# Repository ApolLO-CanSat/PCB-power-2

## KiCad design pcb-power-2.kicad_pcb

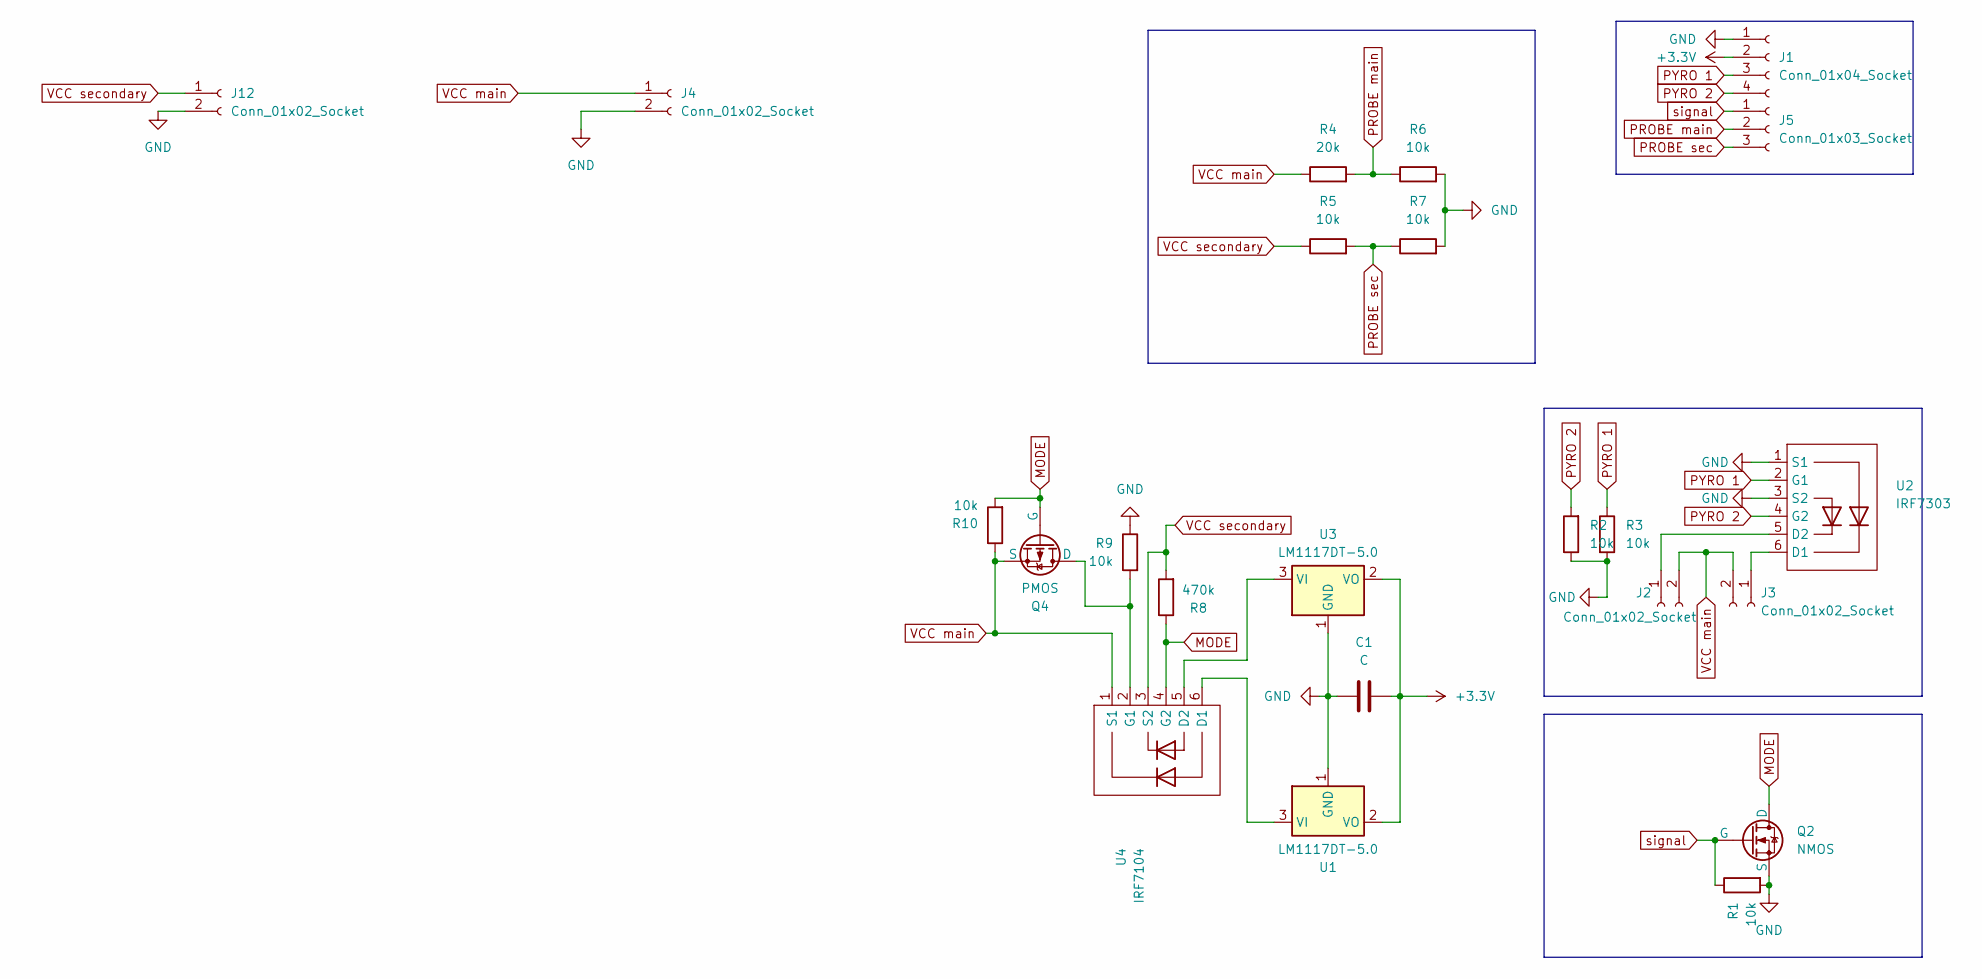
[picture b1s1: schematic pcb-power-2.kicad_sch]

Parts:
C1: C; CP_Radial_D5.0mm_P2.00mm
J1: Conn_01x04_Socket; JST_PH_B4B-PH-K_1x04_P2.00mm_Vertical
J2, J3: Conn_01x02_Socket; TerminalBlock_bornier-2_P5.08mm
J4: Conn_01x02_Socket; JST_PH_B2B-PH-K_1x02_P2.00mm_Vertical
J5: Conn_01x03_Socket; JST_PH_B3B-PH-K_1x03_P2.00mm_Vertical
J12: Conn_01x02_Socket; PinSocket_1x02_P2.54mm_Vertical
Q2: NMOS; SOT-23
Q4: PMOS; TO-252-2
R1, R2, R3, R5, R6, R7, R9, R10: 10k; R_Axial_DIN0207_L6.3mm_D2.5mm_P10.16mm_Horizontal
R4: 20k; R_Axial_DIN0207_L6.3mm_D2.5mm_P10.16mm_Horizontal
R8: 470k; R_Axial_DIN0207_L6.3mm_D2.5mm_P10.16mm_Horizontal
U1, U3: LM1117DT-5.0; TO-252-2
U2: IRF7303
U4: IRF7104

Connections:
+3.3V: C1.2, J1.2, U1.2 (VO), U3.2 (VO)
GND: C1.1, J1.1, J4.2, J12.2, Q2.3 (S), R1.2, R2.1, R3.2, R6.2, R7.2, R9.1, U1.1 (GND), U2.1 (S1), U2.3 (S2), U3.1 (GND)
MODE: Q2.1 (D), Q4.2 (G), R8.1, R10.2, U4.4 (G2)
unnamed: J2.1, U2.5 (D2)
unnamed: J3.1, U2.6 (D1)
unnamed: Q4.1 (D), R9.2, U4.2 (G1)
unnamed: U1.3 (VI), U4.6 (D1)
unnamed: U3.3 (VI), U4.5 (D2)
PROBE main: J5.2, R4.2, R6.1
PROBE sec: J5.3, R5.2, R7.1
PYRO 1: J1.3, R3.1, U2.2 (G1)
PYRO 2: J1.4, R2.2, U2.4 (G2)
VCC main: J2.2, J3.2, J4.1, Q4.3 (S), R4.1, R10.1, U4.1 (S1)
VCC secondary: J12.1, R5.1, R8.2, U4.3 (S2)
signal: J5.1, Q2.2 (G), R1.1

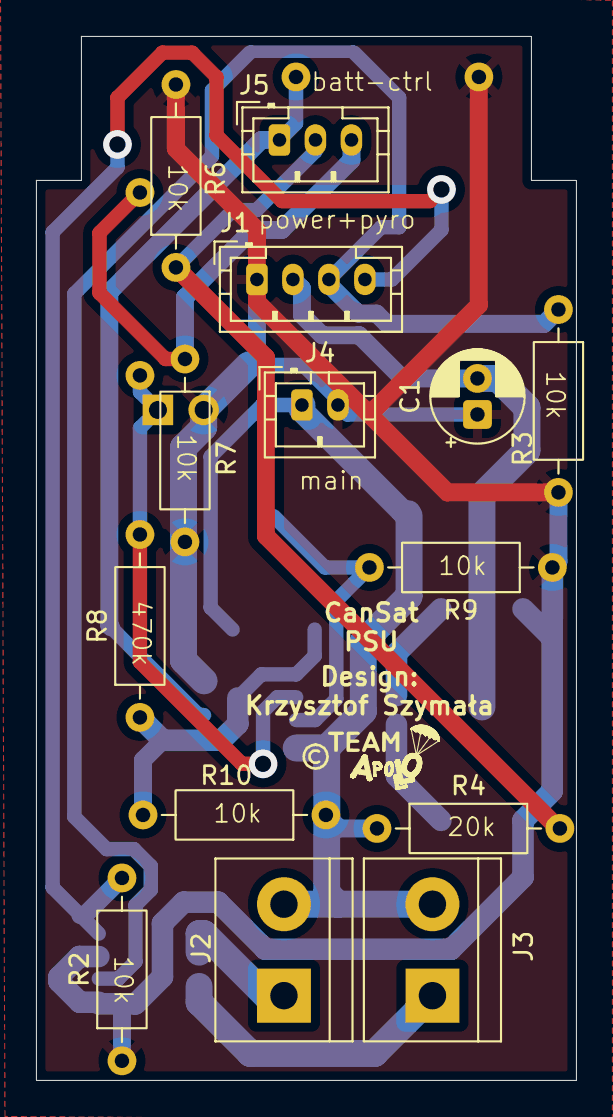
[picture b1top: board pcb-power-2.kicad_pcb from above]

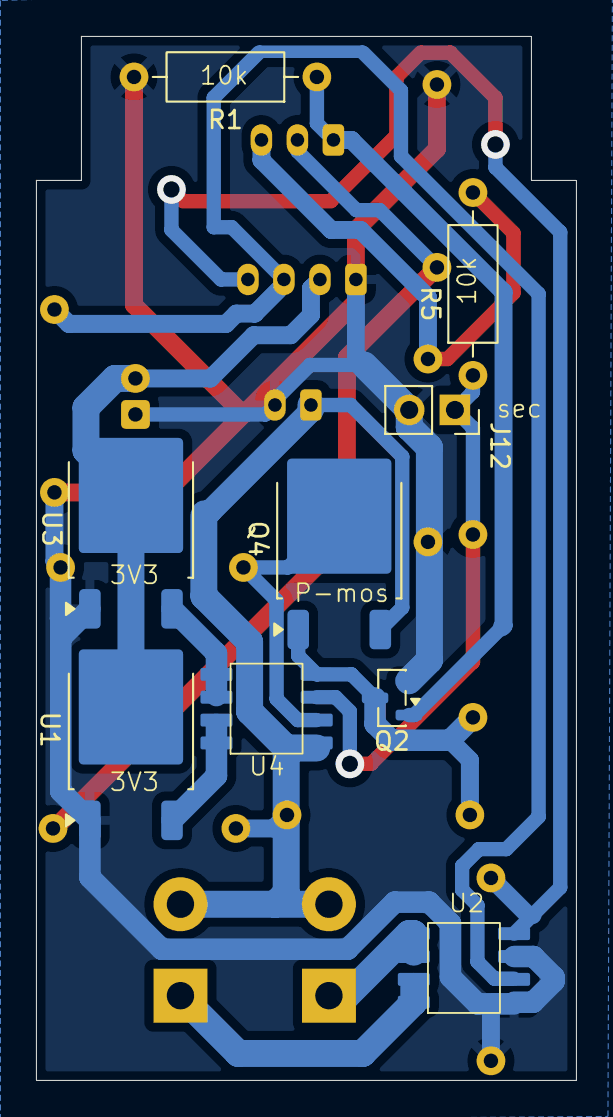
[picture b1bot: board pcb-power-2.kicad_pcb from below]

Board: 2 copper layers, 30.0 x 58.0 mm, 23 parts (9 on the bottom side), 15 nets.

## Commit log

2026-02-27 copied previous repo
2026-02-28 finished pcb design
2026-03-03 corrected P-mosfet connection
2026-03-07 added silkscreen markings
2026-03-13 Changed JST footprints
2026-03-13 Fixed silkscreen
